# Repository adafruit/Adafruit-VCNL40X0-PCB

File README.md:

## Adafruit VCNL40x0 Breakout PCB

<a href="http://www.adafruit.com/products/466"><br/>
Click here to purchase one from the Adafruit shop</a>

PCB files for the Adafruit VCNL4000 and VCNL4010 Breakout PCB. Format is EagleCAD schematic and board layout

For more details, check out the product page at

  * https://www.adafruit.com/product/466

### Description

The VCNL4010 sensor is a nice way to add a small-distance proximity sensor to your microcontroller project. For longer distances (in the range of cm, you can use a SHARP IR distance sensor, but those are only good if the object is over 10 cm away. The VCNL4010 is designed for much shorter distances, no more than 200mm (about 7.5") and under our experimentation we found it worked best at distances of about 10-150mm. It would be good for say detecting when a hand moved nearby, or before a robot smacks into a wall. The sensor also has an ambient light sensor built in.

This sensor is easy to use with any microcontroller that has i2c capability. It is 5 volt compliant so you can use it with 3.3V or 5V logic with no risk of damage. There is an onboard 3.3V ultra low dropout regulator so you can power it with 3.3 to 5.0V. However, if you can give it 5.0V that is ideal since the VIN voltage powers the IR LED and the higher the voltage you can give it, the more powerful it is.

As of Sept 23, 2015 we are now shipping this breakout with the updated VCNL4010 - the library has changed and the chip is slightly different in that it now supports interrupts. We also made the board a little more compact. However, the overall proximity functionality is identical.

### License

Adafruit invests time and resources providing this open source design, please support Adafruit and open-source hardware by purchasing products from [Adafruit](https://www.adafruit.com)!

Designed by Limor Fried/Ladyada for Adafruit Industries.

Creative Commons Attribution/Share-Alike, all text above must be included in any redistribution. See license.txt for additional details.

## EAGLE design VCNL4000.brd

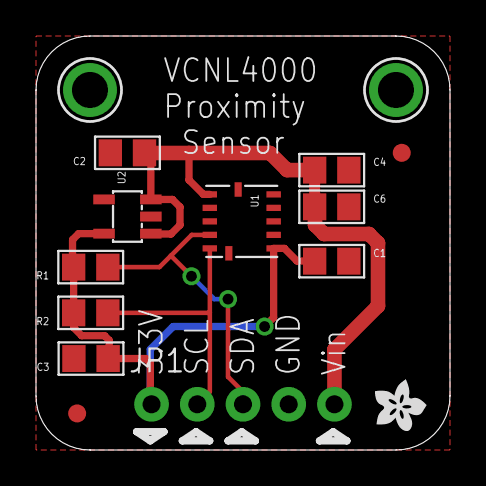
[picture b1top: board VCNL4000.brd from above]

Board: 2 copper layers, 23.0 x 23.0 mm, 15 parts (0 on the bottom side), 5 nets.

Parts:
C1, C2, C4, C6: 10uF; 0805
C3: 0.1uF; 0805
JP1: 1X05_ROUND_76
R1, R2: 10K; 0805
U1: VCNL4000-GS08; VCNL4000
U2: AP7311-33; SOT23-5
U$5, U$6: MOUNTINGHOLE2.0; MOUNTINGHOLE_2.0_PLATED
U$7, U$8: FIDUCIAL; FIDUCIAL_1MM
U$13: ADAFRUIT200MIL

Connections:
3.3V: C1.1, C3.1, JP1.1, R1.2, R2.2, U1.7, U2.5
GND: C1.2, C2.2, C3.2, C4.2, C6.2, JP1.4, U1.6, U1.12, U2.2
SCL: JP1.2, R2.1, U1.5
SDA: JP1.3, R1.1, U1.4
VCC: C2.1, C4.1, C6.1, JP1.5, U1.1, U2.1, U2.3

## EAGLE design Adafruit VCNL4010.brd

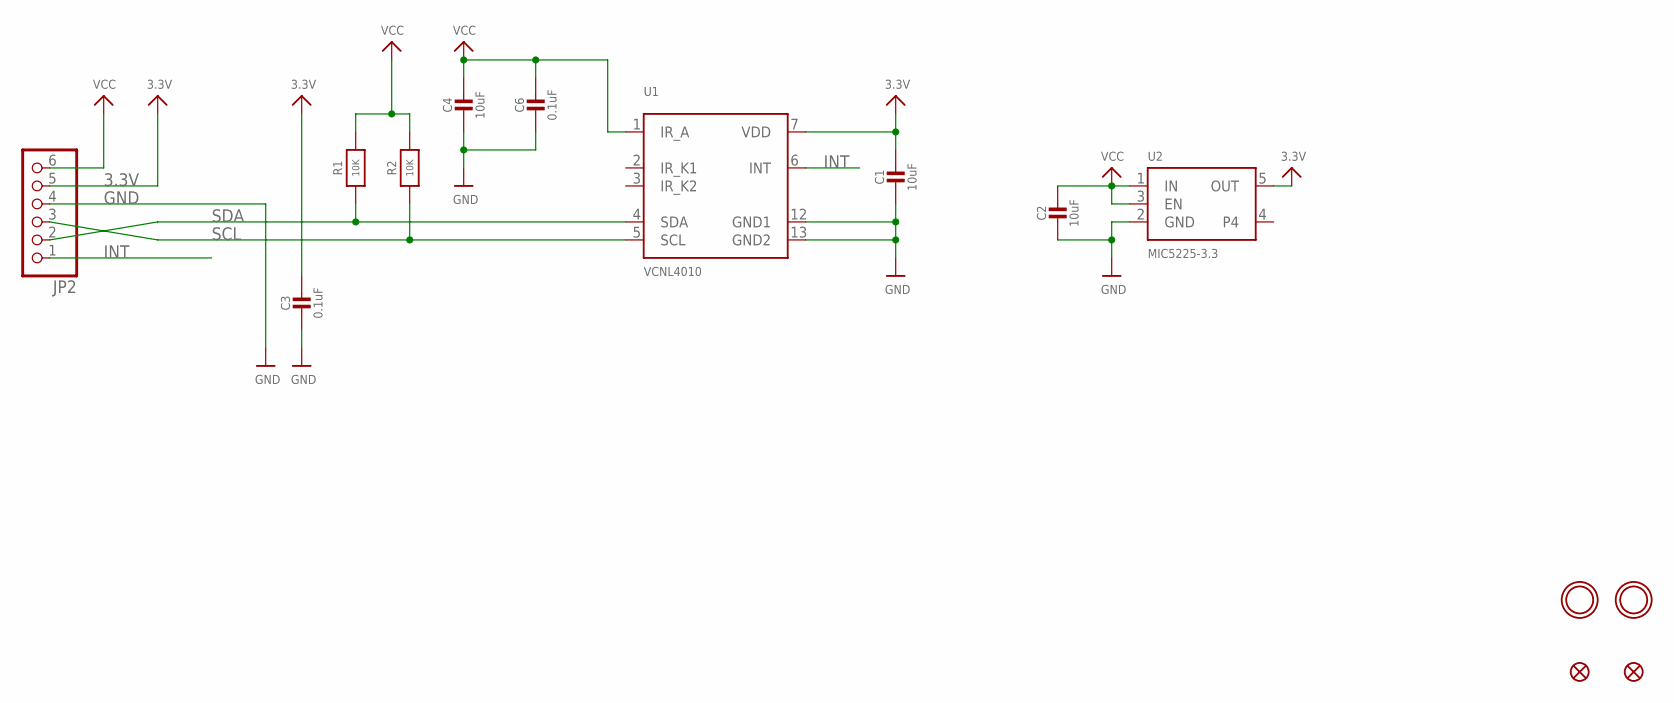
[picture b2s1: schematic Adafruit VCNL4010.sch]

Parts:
C1, C2, C4: 10uF; 0805-NO
C3, C6: 0.1uF; 0805-NO
JP2: HEADER-1X676MIL; 1X06_ROUND_76
R1, R2: 10K; 0805-NO
U1: VCNL4010
U2: MIC5225-3.3; SOT23-5
U$5, U$6: MOUNTINGHOLE2.5; MOUNTINGHOLE_2.5_PLATED
U$7, U$8: FIDUCIAL""; FIDUCIAL_1MM

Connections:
3.3V: C1.1, C3.1, JP2.5, U1.7 (VDD), U2.5 (OUT)
GND: C1.2, C2.2, C3.2, C4.2, C6.2, JP2.4, U1.12 (GND1), U1.13 (GND2), U2.2 (GND)
INT: JP2.1, U1.6 (INT)
SCL: JP2.3, R2.1, U1.5 (SCL)
SDA: JP2.2, R1.1, U1.4 (SDA)
VIN: C2.1, C4.1, C6.1, JP2.6, R1.2, R2.2, U1.1 (IR_A), U2.1 (IN), U2.3 (EN)

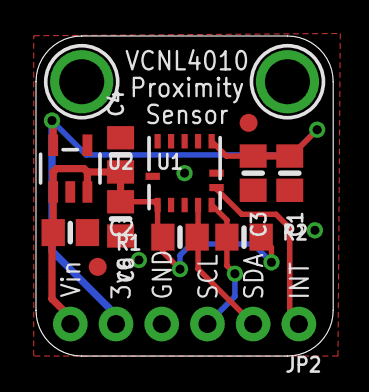
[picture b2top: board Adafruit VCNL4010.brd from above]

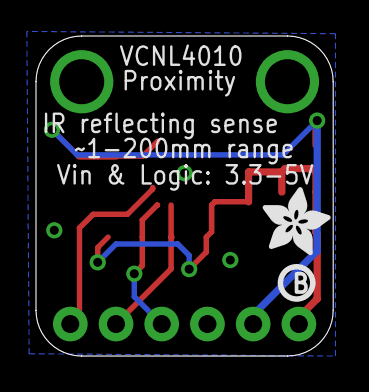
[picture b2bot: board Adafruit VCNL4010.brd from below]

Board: 2 copper layers, 16.5 x 17.8 mm, 16 parts (2 on the bottom side), 6 nets.

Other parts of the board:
U$13: PCBFEAT-REV-040
U$14: ADAFRUIT_3.5MM

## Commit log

2011-10-11 Initial commit - reads proximity and ambient light
2011-10-11 added header
2011-10-11 breakout board files
2011-12-03 Arduino 1.0 compliant
2012-04-17 added delay
2014-02-26 Created Arduino library
2016-09-19 rename
2016-09-19 latest version and a readme
2026-06-03 update file format to XML
